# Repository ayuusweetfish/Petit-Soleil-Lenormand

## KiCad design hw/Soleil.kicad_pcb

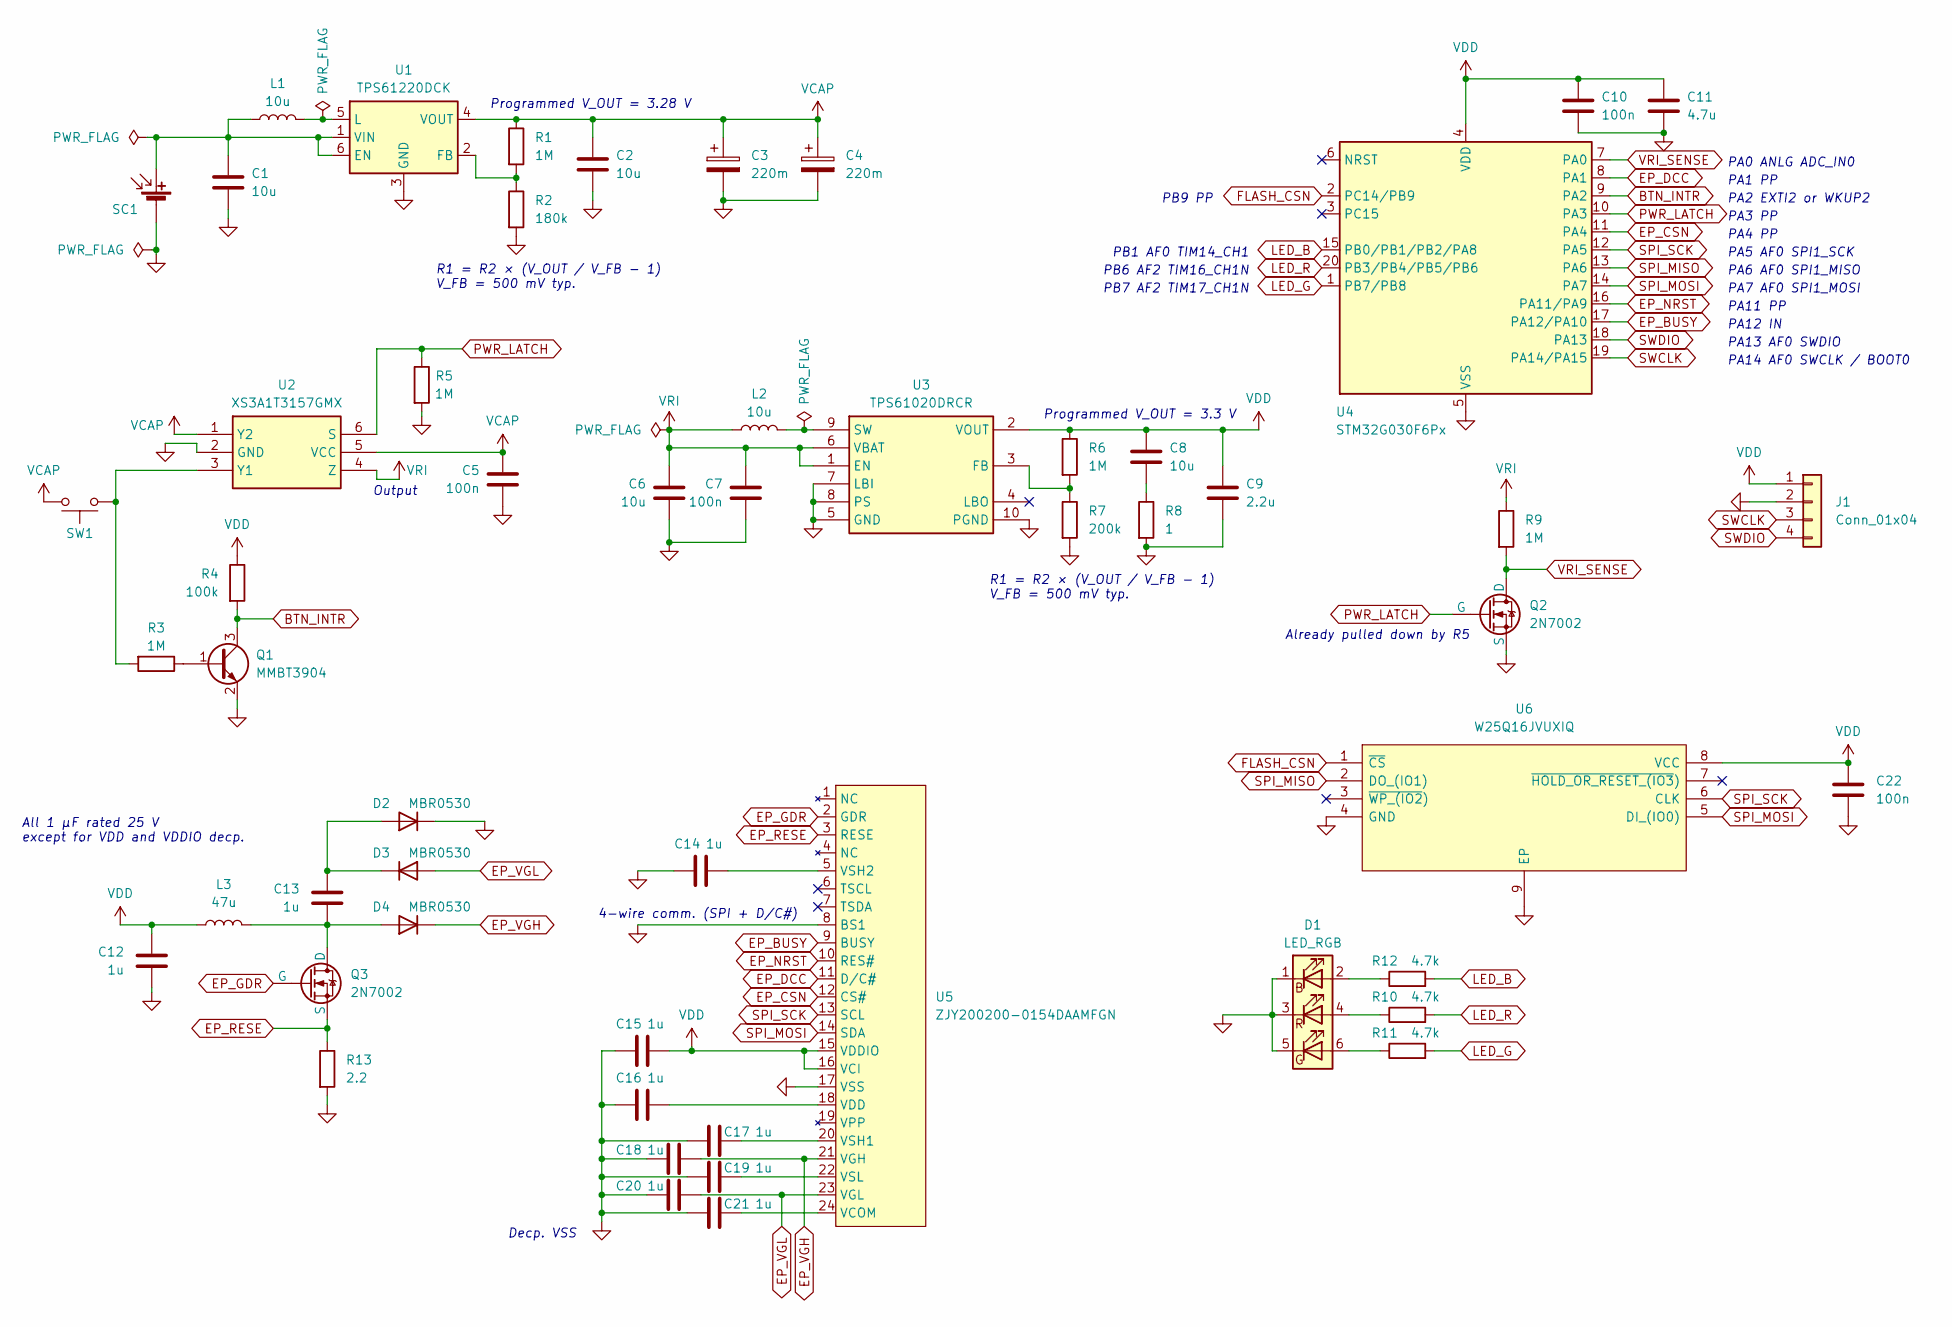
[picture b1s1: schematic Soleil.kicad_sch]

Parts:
C1, C2, C6, C8: 10u; C_0402_1005Metric
C3, C4: 220m; DMS3R3
C5, C7, C10, C22: 100n; C_0402_1005Metric
C9: 2.2u; C_0402_1005Metric
C11: 4.7u; C_0402_1005Metric
C12, C13, C14, C15, C16, C17, C18, C19, C20, C21: 1u; C_0402_1005Metric
D1: LED_RGB; LED_BRG_KA_5050-6
D2, D3, D4: MBR0530; D_SOD-123
J1: Conn_01x04; TestPoints_1x04_P2.0
L1, L2: 10u; L_Sunlord_SWPA252012S
L3: 47u; L_Sunlord_SWPA4020S
Q1: MMBT3904; SOT-23
Q2, Q3: 2N7002; SOT-23
R1, R3, R5, R6, R9: 1M; R_0402_1005Metric
R2: 180k; R_0402_1005Metric
R4: 100k; R_0402_1005Metric
R7: 200k; R_0402_1005Metric
R8: 1; R_0402_1005Metric
R10, R11, R12: 4.7k; R_0402_1005Metric
R13: 2.2; R_0402_1005Metric
SC1: Solar_Cell; SolarPanel_3025
SW1: SW_Push; SW_SPST_TL3342
U1: TPS61220DCK; Texas_R-PDSO-G6
U2: XS3A1T3157GMX; Manufacturer_Part_Number XS3A1T3157GMX; Mouser Part Number 771-XS3A1T3157GMX
U3: TPS61020DRCR; Manufacturer_Part_Number TPS61020DRCR; Mouser Part Number 595-TPS61020DRCR
U4: STM32G030F6Px; TSSOP-20_4.4x6.5mm_P0.65mm
U5: ZJY200200-0154DAAMFGN; FPC_1x24_P0.5
U6: W25Q16JVUXIQ; SON50P300X200X60-9N; Manufacturer_Part_Number W25Q16JVUXIQ

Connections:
BTN_INTR: Q1.3 (C), R4.2, U4.9 (PA2)
EP_BUSY: U4.17 (PA12/PA10), U5.9 (BUSY)
EP_CSN: U4.11 (PA4), U5.12 (CS#)
EP_DCC: U4.8 (PA1), U5.11 (D/C#)
EP_GDR: Q3.1 (G), U5.2 (GDR)
EP_NRST: U4.16 (PA11/PA9), U5.10 (RES#)
EP_RESE: Q3.2 (S), R13.1, U5.3 (RESE)
EP_VGH: C18.2, D4.1 (K), U5.21 (VGH)
EP_VGL: C20.2, D3.2 (A), U5.23 (VGL)
FLASH_CSN: U4.2 (PC14/PB9), U6.1 (~CS)
GND: C1.2, C2.2, C3.2, C4.2, C5.1, C6.2, C7.2, C9.2, C10.1, C11.1, C12.2, C14.1, C15.1, C16.1, C17.1, C18.1, C19.1, C20.1, C21.1, C22.1, D1.1 (BK), D1.3 (RK), D1.5 (GK), D2.1 (K), J1.2, Q1.2 (E), Q2.2 (S), R2.2, R5.2, R7.2, R8.2, R13.2, SC1.2 (-), U1.3 (GND), U2.2 (GND), U3.5 (GND), U3.7 (LBI), U3.8 (PS), U3.10 (PGND), U3.11 (EP/PGND_1), U3.A11 (EP/PGND_2), U3.B11 (EP/PGND_3), U3.C11 (EP/PGND_4), U3.D11 (EP/PGND_5), U4.5 (VSS), U5.8 (BS1), U5.17 (VSS), U6.4 (GND), U6.9 (EP)
LED_B: R12.2, U4.15 (PB0/PB1/PB2/PA8)
LED_G: R11.2, U4.1 (PB7/PB8)
LED_R: R10.2, U4.20 (PB3/PB4/PB5/PB6)
unnamed: C8.2, R8.1
unnamed: D1.2 (BA), R12.1
unnamed: D1.6 (GA), R11.1
unnamed: D1.4 (RA), R10.1
unnamed: C13.1, D2.2 (A), D3.1 (K)
unnamed: C13.2, D4.2 (A), L3.2, Q3.3 (D)
unnamed: Q1.1 (B), R3.1
unnamed: C1.1, L1.1, SC1.1 (+), U1.1 (VIN), U1.6 (EN)
unnamed: R1.2, R2.1, U1.2 (FB)
unnamed: L1.2, U1.5 (L)
unnamed: R3.2, SW1.2, U2.3 (Y1)
unnamed: R6.2, R7.1, U3.3 (FB)
unnamed: L2.2, U3.9 (SW)
unnamed: C21.2, U5.24 (VCOM)
unnamed: C16.2, U5.18 (VDD)
unnamed: C17.2, U5.20 (VSH1)
unnamed: C14.2, U5.5 (VSH2)
unnamed: C19.2, U5.22 (VSL)
PWR_LATCH: Q2.1 (G), R5.1, U2.6 (S), U4.10 (PA3)
SPI_MISO: U4.13 (PA6), U6.2 (DO_(IO1))
SPI_MOSI: U4.14 (PA7), U5.14 (SDA), U6.5 (DI_(IO0))
SPI_SCK: U4.12 (PA5), U5.13 (SCL), U6.6 (CLK)
SWCLK: J1.3, U4.19 (PA14/PA15)
SWDIO: J1.4, U4.18 (PA13)
VCAP: C2.1, C3.1, C4.1, C5.2, R1.1, SW1.1, U1.4 (VOUT), U2.1 (Y2), U2.5 (VCC)
VDD: C8.1, C9.1, C10.2, C11.2, C12.1, C15.2, C22.2, J1.1, L3.1, R4.1, R6.1, U3.2 (VOUT), U4.4 (VDD), U5.15 (VDDIO), U5.16 (VCI), U6.8 (VCC)
VRI: C6.1, C7.1, L2.1, R9.1, U2.4 (Z), U3.1 (EN), U3.6 (VBAT)
VRI_SENSE: Q2.3 (D), R9.2, U4.7 (PA0)

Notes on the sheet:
PA12 IN
Programmed V_OUT = 3.3 V
PB7 AF2 TIM17_CH1N
PA11 PP
PA3 PP
PA7 AF0 SPI1_MOSI
4-wire comm. (SPI + D/C#)
PB6 AF2 TIM16_CH1N
PB1 AF0 TIM14_CH1
PB9 PP
R1 = R2 × (V_OUT / V_FB - 1) V_FB = 500 mV typ.
Decp. VSS
All 1 µF rated 25 V except for VDD and VDDIO decp.
PA1 PP
PA0 ANLG ADC_IN0
PA4 PP
PA5 AF0 SPI1_SCK
Already pulled down by R5
Output
PA14 AF0 SWCLK / BOOT0
PA6 AF0 SPI1_MISO
Programmed V_OUT = 3.28 V
PA2 EXTI2 or WKUP2
PA13 AF0 SWDIO

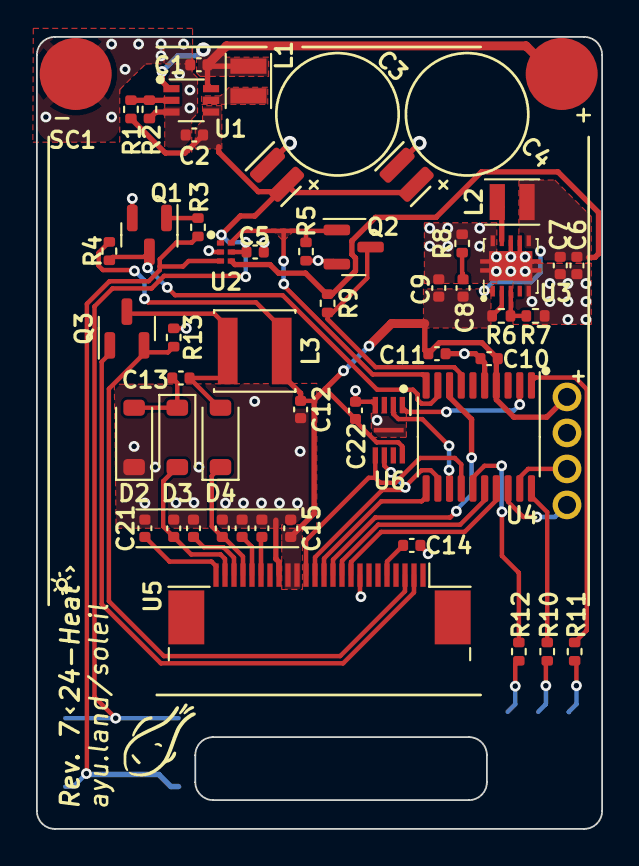
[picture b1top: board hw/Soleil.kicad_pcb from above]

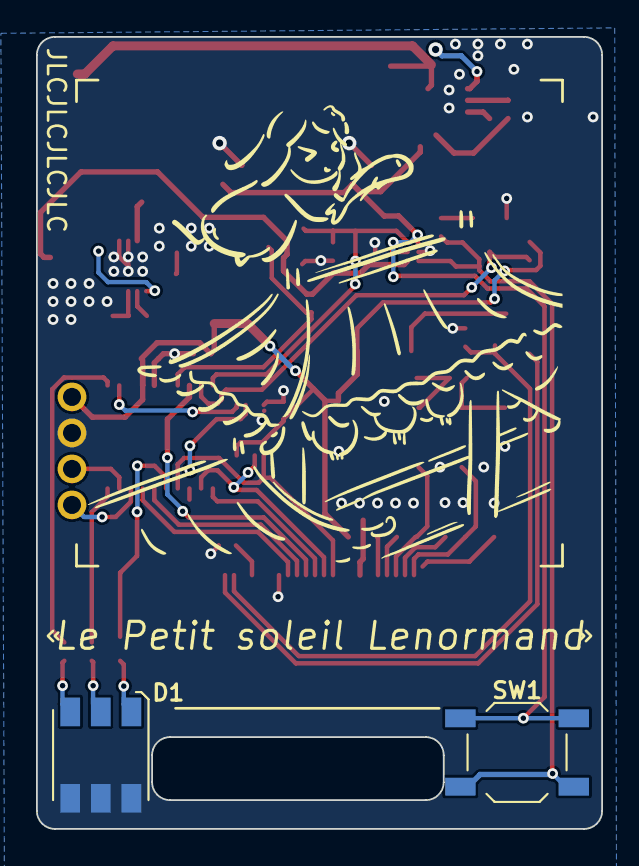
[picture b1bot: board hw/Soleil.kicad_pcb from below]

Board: 2 copper layers, 31.4 x 44.0 mm, 54 parts (2 on the bottom side), 42 nets.

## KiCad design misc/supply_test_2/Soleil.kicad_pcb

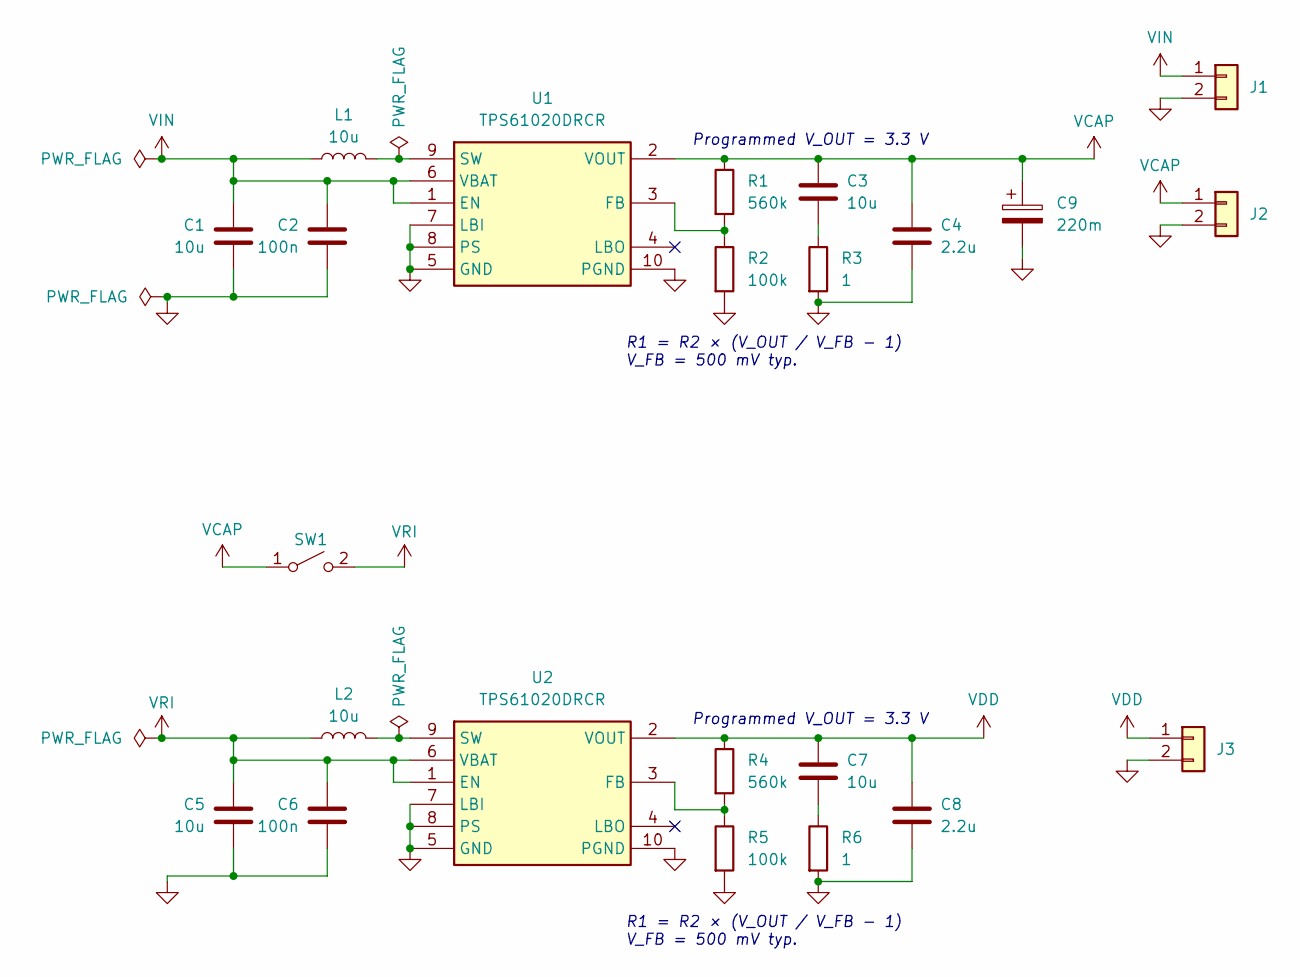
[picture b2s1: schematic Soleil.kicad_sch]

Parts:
C1, C3, C5, C7: 10u; C_0603_1608Metric
C2, C6: 100n; C_0603_1608Metric
C4, C8: 2.2u; C_0603_1608Metric
C9: 220m; DMS3R3
J1, J2, J3: Conn_01x02; PinHeader_1x02_P2.54mm_Vertical
L1, L2: 10u; L_Sunlord_SWPA252012S
R1, R4: 560k; R_0402_1005Metric
R2, R5: 100k; R_0402_1005Metric
R3, R6: 1; R_0402_1005Metric
SW1: SW_SPST; SPST_1x01_P2.54
U1, U2: TPS61020DRCR; Manufacturer_Part_Number TPS61020DRCR; Mouser Part Number 595-TPS61020DRCR

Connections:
GND: C1.2, C2.2, C4.2, C5.2, C6.2, C8.2, C9.2, J1.2, J2.2, J3.2, R2.2, R3.2, R5.2, R6.2, U1.5 (GND), U1.7 (LBI), U1.8 (PS), U1.10 (PGND), U1.11 (EP/PGND_1), U1.A11 (EP/PGND_2), U1.B11 (EP/PGND_3), U1.C11 (EP/PGND_4), U1.D11 (EP/PGND_5), U2.5 (GND), U2.7 (LBI), U2.8 (PS), U2.10 (PGND), U2.11 (EP/PGND_1), U2.A11 (EP/PGND_2), U2.B11 (EP/PGND_3), U2.C11 (EP/PGND_4), U2.D11 (EP/PGND_5)
unnamed: C3.2, R3.1
unnamed: C7.2, R6.1
unnamed: R1.2, R2.1, U1.3 (FB)
unnamed: L1.2, U1.9 (SW)
unnamed: R4.2, R5.1, U2.3 (FB)
unnamed: L2.2, U2.9 (SW)
VCAP: C3.1, C4.1, C9.1, J2.1, R1.1, SW1.1 (A), U1.2 (VOUT)
VDD: C7.1, C8.1, J3.1, R4.1, U2.2 (VOUT)
VIN: C1.1, C2.1, J1.1, L1.1, U1.1 (EN), U1.6 (VBAT)
VRI: C5.1, C6.1, L2.1, SW1.2 (B), U2.1 (EN), U2.6 (VBAT)

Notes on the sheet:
Programmed V_OUT = 3.3 V
R1 = R2 × (V_OUT / V_FB - 1) V_FB = 500 mV typ.

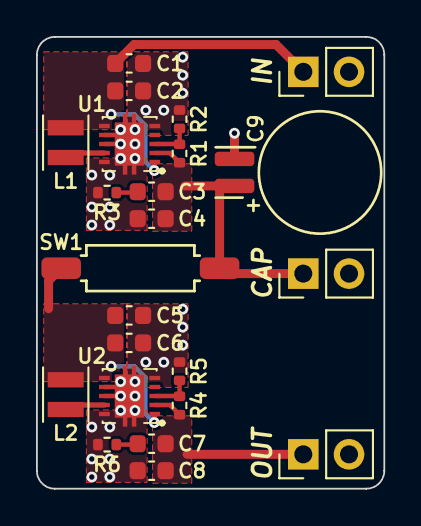
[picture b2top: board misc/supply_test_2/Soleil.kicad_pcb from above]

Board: 2 copper layers, 19.3 x 25.1 mm, 23 parts (0 on the bottom side), 11 nets.

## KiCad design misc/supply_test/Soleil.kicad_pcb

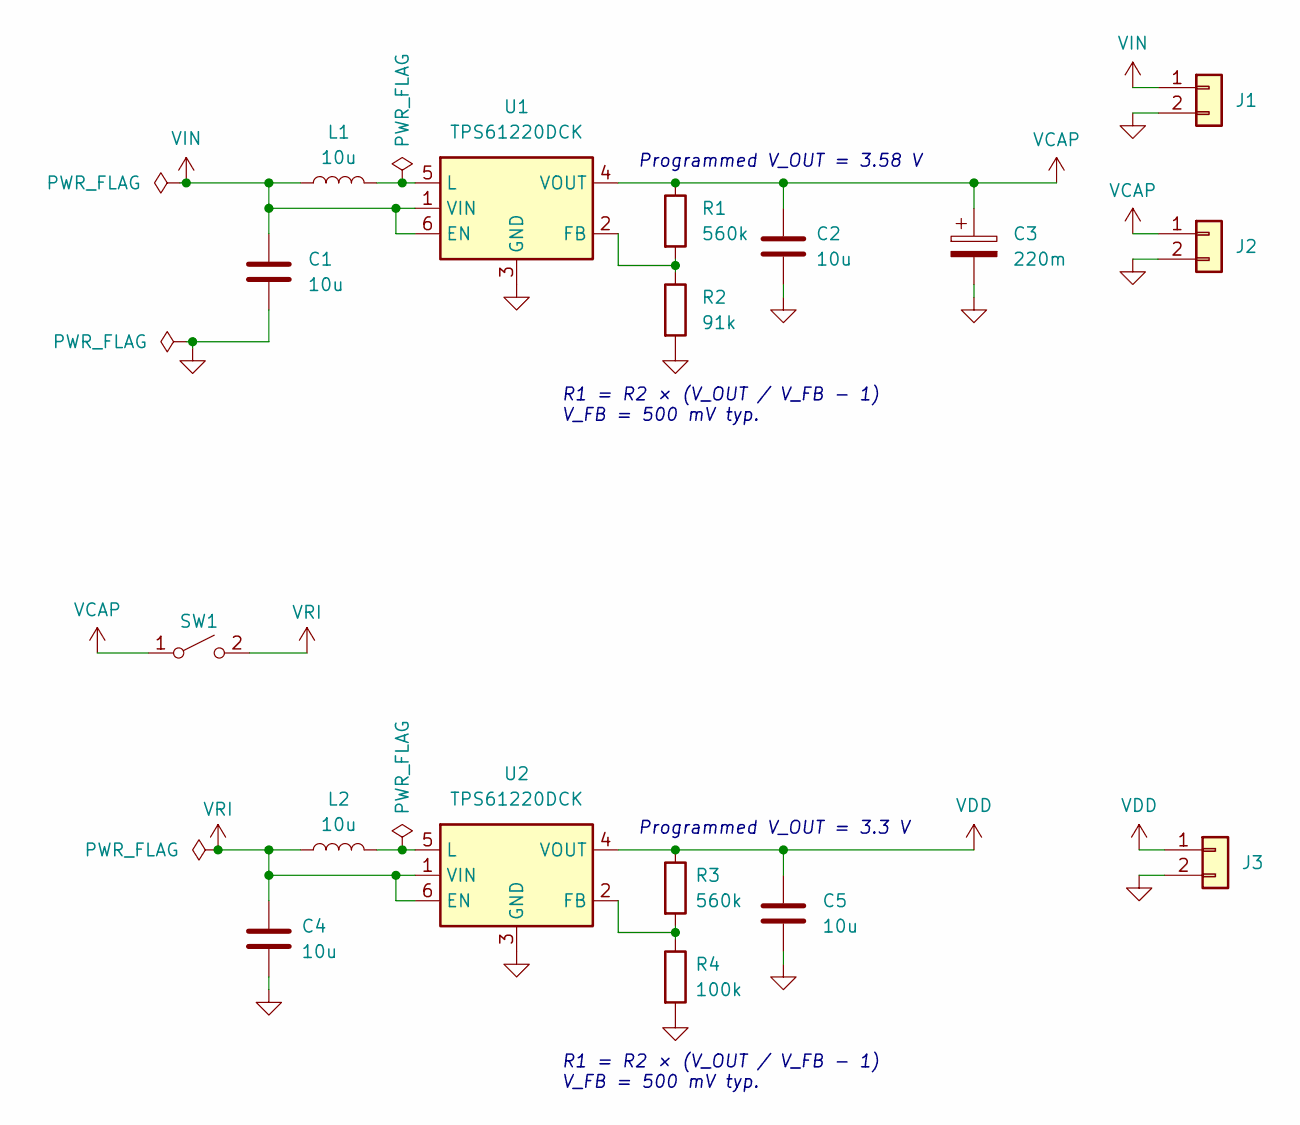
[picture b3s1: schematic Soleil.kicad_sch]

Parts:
C1, C2, C4, C5: 10u; C_0603_1608Metric
C3: 220m; DMS3R3
J1, J2, J3: Conn_01x02; PinHeader_1x02_P2.54mm_Vertical
L1, L2: 10u; L_Sunlord_SWPA252012S
R1, R3: 560k; R_0603_1608Metric
R2: 91k; R_0603_1608Metric
R4: 100k; R_0603_1608Metric
SW1: SW_SPST; SPST_1x01_P2.54
U1, U2: TPS61220DCK; Texas_R-PDSO-G6

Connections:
GND: C1.2, C2.2, C3.2, C4.2, C5.2, J1.2, J2.2, J3.2, R2.2, R4.2, U1.3 (GND), U2.3 (GND)
unnamed: R1.2, R2.1, U1.2 (FB)
unnamed: L1.2, U1.5 (L)
unnamed: R3.2, R4.1, U2.2 (FB)
unnamed: L2.2, U2.5 (L)
VCAP: C2.1, C3.1, J2.1, R1.1, SW1.1 (A), U1.4 (VOUT)
VDD: C5.1, J3.1, R3.1, U2.4 (VOUT)
VIN: C1.1, J1.1, L1.1, U1.1 (VIN), U1.6 (EN)
VRI: C4.1, L2.1, SW1.2 (B), U2.1 (VIN), U2.6 (EN)

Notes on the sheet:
Programmed V_OUT = 3.58 V
R1 = R2 × (V_OUT / V_FB - 1) V_FB = 500 mV typ.
Programmed V_OUT = 3.3 V

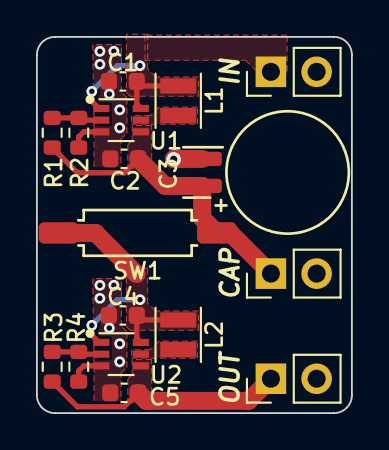
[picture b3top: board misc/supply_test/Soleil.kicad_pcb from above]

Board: 2 copper layers, 17.5 x 20.9 mm, 17 parts (0 on the bottom side), 9 nets.

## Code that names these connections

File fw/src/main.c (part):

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#include "../misc/rng/twofish.h"
#include "../misc/rng/xoodoo.h"

#define PIN_LED_R     GPIO_PIN_4
#define PIN_LED_G     GPIO_PIN_7
#define PIN_LED_B     GPIO_PIN_1
#define PIN_EP_NCS    GPIO_PIN_4
#define PIN_EP_DCC    GPIO_PIN_1
#define PIN_EP_NRST   GPIO_PIN_11
#define PIN_EP_BUSY   GPIO_PIN_12
#define EXTI_LINE_EP_BUSY EXTI_LINE_12
#define PIN_BUTTON    GPIO_PIN_2
#define EXTI_LINE_BUTTON  EXTI_LINE_2
#define PIN_PWR_LATCH GPIO_PIN_3

#include "debug_printf.h"

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static inline void _epd_cmd(uint8_t cmd, const uint8_t *params, size_t params_size)
{
  HAL_GPIO_WritePin(GPIOA, PIN_EP_NCS, GPIO_PIN_RESET);
  HAL_GPIO_WritePin(GPIOA, PIN_EP_DCC, GPIO_PIN_RESET);
  spi_transmit(&cmd, 1);
  HAL_GPIO_WritePin(GPIOA, PIN_EP_DCC, GPIO_PIN_SET);
  if (params_size > 0) {
    spi_transmit(params, params_size);
  }
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static inline void epd_read(uint8_t cmd, uint8_t *out_buf, size_t out_buf_size)
{
  HAL_GPIO_WritePin(GPIOA, PIN_EP_NCS, GPIO_PIN_RESET);
  HAL_GPIO_WritePin(GPIOA, PIN_EP_DCC, GPIO_PIN_RESET);
  spi_transmit(&cmd, 1);
  HAL_GPIO_WritePin(GPIOA, PIN_EP_DCC, GPIO_PIN_SET);
  spi_receive(out_buf, out_buf_size);
  HAL_GPIO_WritePin(GPIOA, PIN_EP_NCS, GPIO_PIN_SET);
}

static inline void epd_waitbusy()
{
  // Wait for PIN_EP_BUSY to go low

  sleep_delay(2); // Some operations are short, branch off early

  while (GPIOA->IDR & PIN_EP_BUSY) {
#if ENABLE_SLEEP
    HAL_SuspendTick();
    rtc_waiting_for = RTC_WAITING_FOR_EP_BUSY;
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
    // If the busy pin is still actually high, enter Stop 1 mode
    PWR->CR1 = (PWR->CR1 & ~PWR_CR1_LPMS) | PWR_CR1_LPMS_0;
    if (GPIOA->IDR & PIN_EP_BUSY) {
      SCB->SCR |= SCB_SCR_SLEEPDEEP_Msk;
      __WFI();
      SCB->SCR &= ~SCB_SCR_SLEEPDEEP_Msk;
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static void epd_reset(bool partial, bool power_save)
{
  // (1) HW & SW Reset
  HAL_GPIO_WritePin(GPIOA, PIN_EP_NRST, GPIO_PIN_RESET);
  sleep_delay(10);
  HAL_GPIO_WritePin(GPIOA, PIN_EP_NRST, GPIO_PIN_SET);
  sleep_delay(10);
  epd_waitbusy();
  // SW RESET
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
  uint8_t cmd = 0x27;
  HAL_GPIO_WritePin(GPIOA, PIN_EP_NCS, GPIO_PIN_RESET);
  HAL_GPIO_WritePin(GPIOA, PIN_EP_DCC, GPIO_PIN_RESET);
  spi_transmit(&cmd, 1);
  HAL_GPIO_WritePin(GPIOA, PIN_EP_DCC, GPIO_PIN_SET);
  spi_receive((uint8_t *)ram, 1); // Dummy byte
  for (int i = 0; i < 32; i++) {
    spi_receive((uint8_t *)ram, n * 4);
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  __HAL_RCC_GPIOB_CLK_ENABLE();
  GPIO_InitTypeDef gpio_init;

  // SWD (PA13, PA14)
  gpio_init.Pin = GPIO_PIN_13 | GPIO_PIN_14;
  gpio_init.Mode = GPIO_MODE_AF_PP; // Pass over control to AF peripheral
  gpio_init.Alternate = GPIO_AF0_SWJ;
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
  // ======= Power latch ======
  gpio_init = (GPIO_InitTypeDef){
    .Pin = PIN_PWR_LATCH,
    .Mode = GPIO_MODE_OUTPUT_PP,
    .Pull = GPIO_NOPULL,
    .Speed = GPIO_SPEED_FREQ_LOW,
  };
  HAL_GPIO_Init(GPIOA, &gpio_init);
  HAL_GPIO_WritePin(GPIOA, PIN_PWR_LATCH, 1);

  // ======== Clocks ========
  setup_clocks();
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
  // Activate EPD driver (SSD1681) reset signal
  gpio_init = (GPIO_InitTypeDef){
    .Pin = PIN_EP_NRST,
    .Mode = GPIO_MODE_OUTPUT_PP,
    .Pull = GPIO_NOPULL,
    .Speed = GPIO_SPEED_FREQ_LOW,
  };
  HAL_GPIO_Init(GPIOA, &gpio_init);
  HAL_GPIO_WritePin(GPIOA, PIN_EP_NRST, 0);

  // ======== Button ========
  gpio_init.Pin = PIN_BUTTON;
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    uint32_t t0 = HAL_GetTick();
    while (GPIOA->IDR & PIN_BUTTON) {
      if (HAL_GetTick() - t0 >= timeout_seconds * 1000) {
        HAL_GPIO_WritePin(GPIOA, PIN_PWR_LATCH, 0);
        while (1) { }
      }
    }
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
  // ======== SPI ========
  // GPIO ports
  // SPI1_SCK (PA5), SPI1_MISO (PA6), SPI1_MOSI (PA7)
  gpio_init.Pin = GPIO_PIN_5 | GPIO_PIN_6 | GPIO_PIN_7;
  gpio_init.Mode = GPIO_MODE_AF_PP;
  gpio_init.Alternate = GPIO_AF0_SPI1;
  gpio_init.Pull = GPIO_NOPULL;
  gpio_init.Speed = GPIO_SPEED_FREQ_HIGH;
  HAL_GPIO_Init(GPIOA, &gpio_init);
  // Output FLASH_CSN (PB9)
  HAL_GPIO_Init(GPIOB, &(GPIO_InitTypeDef){
    .Pin = GPIO_PIN_9,
    .Mode = GPIO_MODE_OUTPUT_PP,
  });
  HAL_GPIO_WritePin(GPIOB, GPIO_PIN_9, 1);
  // Output EP_CSN (PA4), EP_DCC (PA6 (Rev. 4) / PA1 (Rev. 5))
  // EP_NRST (PA11) is initialised earlier
  gpio_init.Pin = PIN_EP_NCS | PIN_EP_DCC;
  gpio_init.Mode = GPIO_MODE_OUTPUT_PP;
  gpio_init.Pull = GPIO_NOPULL;
  HAL_GPIO_Init(GPIOA, &gpio_init);
  HAL_GPIO_WritePin(GPIOA, PIN_EP_NCS, 1);
  // while (HAL_GPIO_ReadPin(GPIOA, PIN_EP_NCS) == 0) { }
  HAL_GPIO_WritePin(GPIOA, PIN_EP_DCC, 0);
  HAL_GPIO_WritePin(GPIOA, PIN_EP_NRST, 0);
  // Input EP_BUSY (PA12)
  gpio_init.Pin = PIN_EP_BUSY;
  gpio_init.Mode = GPIO_MODE_INPUT;
  gpio_init.Pull = GPIO_PULLDOWN;
  HAL_GPIO_Init(GPIOA, &gpio_init);
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    // EPD
    if (n_cards == 1) {
      if (epd_state == 0 && t >= 30) {
        HAL_GPIO_WritePin(GPIOA, PIN_EP_NRST, GPIO_PIN_RESET);
        epd_state = 1;
      } else if (epd_state == 1 && t >= 50) {
        HAL_GPIO_WritePin(GPIOA, PIN_EP_NRST, GPIO_PIN_SET);
        epd_state = 2;
      } else if (epd_state == 2 && t >= 70) {
        epd_waitbusy();
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
if (0) {
  display_image(-1);
  HAL_GPIO_WritePin(GPIOA, PIN_PWR_LATCH, 0);
  while (1) { }
}

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    }
  }

  HAL_GPIO_WritePin(GPIOA, PIN_PWR_LATCH, 0);
  HAL_SuspendTick();
  HAL_PWR_EnterSTOPMode(PWR_LOWPOWERREGULATOR_ON, PWR_STOPENTRY_WFI);
  while (1) { }
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    setup_clocks();
    stopped = false;
  }
  __HAL_GPIO_EXTI_CLEAR_IT(PIN_EP_BUSY);
}

void TIM3_IRQHandler()
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  else return;

  HAL_GPIO_Init(GPIOB, &(GPIO_InitTypeDef){
    .Pin = PIN_LED_R,
    .Mode = GPIO_MODE_OUTPUT_PP,
  });
  if (rtc_waiting_for == RTC_WAITING_FOR_BTN) {
    // Turn off
    HAL_GPIO_WritePin(GPIOA, PIN_PWR_LATCH, 0);
    // Indicate status when the debug probe is connected
    for (int i = 0; ; i++) {
      GPIOB->BSRR = PIN_LED_R << 16; spin_delay(16000 * 40);
      GPIOB->BSRR = PIN_LED_R <<  0; spin_delay(16000 * 40);
    }
  } else if (rtc_waiting_for == RTC_WAITING_FOR_EP_BUSY) {
    // EPD busy stays high, try system reset (most probably a soldering defect!)
    for (int i = 0; i < 5; i++) {
      GPIOB->BSRR = PIN_LED_R <<  0; spin_delay(16000 * 40);
      GPIOB->BSRR = PIN_LED_R << 16; spin_delay(16000 * 40);
    }
    NVIC_SystemReset();
  }
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
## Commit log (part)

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2023-11-28 🎉 Blink
2023-11-28 Writing EPD
2023-11-28 Read ADC
2023-11-28 Release power latch after 10 blinks
2023-11-28 Write display and power off
2023-12-23 Sort-out; add hardware design
2023-12-23 (WIP) Update PCB layout, routing to-do
2023-12-23 Finish routing for the updated board
2023-12-23 Change LED to SMD RGB; submit for fabrication
2023-12-23 Add CAD files for EPD dimensions
2023-12-31 Blink on the updated hardware
2024-01-03 Test RGB LED PWM output with rotating hues
2024-02-29 Revise schematic
2024-02-29 Revise circuit board design; submit for fab
2024-03-08 Update firmware to match revised hardware
2024-03-08 Enable PLL; add pauses between lighting cycles
2024-03-09 Enable EXTI interrupt
2024-03-09 Enter Stop mode and wake up by button press
2024-03-09 Enter Stop 1 mode when idle and resume on button press
2024-03-09 Update EPD (?)
2024-03-09 Fix corrupted memory
2024-03-09 Inspect entropy sources
2024-03-09 Add SRAM state as an entropy source
2024-03-12 Add back partial refreshes
2024-03-12 Count LSI as an entropy source
2024-03-15 Revise and simplify schematic
2024-03-16 Revise board design; submit for fab (Rev. 5)
2024-03-17 Read factory clock calibration as a source of device signature
2024-03-18 Add Twofish implementation
2024-03-18 Switch to Brian Gladman's Twofish implementation
2024-03-18 Adapt Twofish impl. as a header-only library
2024-03-19 Add satellite images
2024-03-19 Add Meteosat IR data from EUMETSAT
2024-03-19 Extend sources by multiple data endpoints from each entity
2024-03-19 Normalise all returned payload to Uint8Array
2024-03-19 Use SHAKE256 for an overall digest
2024-03-19 (WIP) Periodic checks
2024-03-19 Use `Deno.cron` for scheduling
2024-03-20 Implement running pre-commitment
2024-03-20 Save miscellaneous random blocks
2024-03-20 Properly report rejections in misc. block crafting
2024-03-20 Fix too recent timestamp for misc. entropy collection
2024-03-20 Add FY WV back to public sources with timestamp offset
2024-03-20 Fix misspelled Cron schedule
2024-03-20 Eliminate redundant initialization on startup
2024-03-21 Mix in previous output
2024-03-21 Load previous block on startup
2024-03-21 Trace back in time for backup/debug usage
2024-03-21 (WIP) Adapt firmware pin definitions to Rev. 5 hardware
2024-03-21 Add HTTP endpoint
2024-03-21 Report error messages on currently missing sources
2024-03-21 Added short and plain formatted endpoints
2024-03-21 Report previous pulse at root URL
2024-03-21 Fix romanticisation of Elektro-L
2024-03-21 Properly store messages and image URLs
2024-03-21 Keep reporting source URLs for current pulse after finalisation
2024-03-21 Fix falsely reporting null output for current pulse on distributed deploy environments
2024-03-22 🚧 Debugging hardware
2024-03-23 Revise hardware; fix phantom powering
2024-03-23 🚧 Further revise hardware
2024-03-23 Revise hardware and submit for fabrication (Rev. 6)
2024-03-25 Add Ayu.land log digest as a miscellaneous source
2024-03-25 Add webpage placeholders
2024-03-26 Keep URLs and messages for 24 hours
2024-03-26 Serve static page contents
2024-03-26 Automatically process and subset font
2024-03-27 Tweak page appearance on mobile devices
2024-03-27 Add OpenSky Network as a miscellaneous source
2024-03-28 Add hash verification implementation in C
2024-03-28 Simplify C implementation
2024-03-28 Implement lookup-based web page template
2024-03-28 Add monospace text
2024-03-28 Add complete verification steps to the page
2024-03-28 Fix incorrect precommitment check instruction
2024-03-29 Cache images from INSAT
2024-03-29 Display timestamps on web page
2024-03-29 Log modification timestamps and sizes of fetched images
2024-03-29 Use full font file during development
2024-03-29 Add banner background image
2024-03-30 Revise web page
2024-03-30 Fix large files not written to cache database
2024-03-30 Implement a file cache server
2024-03-30 Migrate to the external cache server
2024-03-30 A few clean-up fixes
2024-03-30 More clean-up fixes
2024-03-30 More > <
2024-03-30 Fix incongruences in the C hash implementation
2024-03-30 Automatically prune cached files older than a day
2024-03-31 Support multiple pages
2024-03-31 Revise web pages
2024-03-31 Add titles to pages
2024-03-31 Store language selection in cookies
2024-03-31 Minor appearance tweaks
2024-03-31 Keep mixing in the last pulse with possibly skipped ones
2024-03-31 Workaround for frozen cron jobs on Deploy?
2024-03-31 Fix SDO/AIA 193 misc. source rejected due to timestamp offset
2024-04-01 Cache template lookup from previous pulse
2024-04-01 Tweak web pages
2024-04-03 Test with STOP mode on startup
2024-04-03 Debug switch erroneously left on
2024-04-05 Replace INSAT source with a more frequently updated one
2024-04-05 Deutscher Wetterdienst's WMC?
2024-04-06 🚧 Update beacon web page
2024-04-06 Minor page style fixes
2024-04-07 Proxy emojis
2024-04-07 Why edit the pages yet another time?
2024-05-31 Add power supply test (Rev. 6/T)
2024-05-31 Revise text style; submit for fab
2024-07-13 Add supply test 2 (with TPS61020)
2024-07-17 Add minimal power consumption test firmware
2024-07-17 Revise main firmware with testing interactions?
2024-07-18 Update layout, 🚧 routing to-do
2024-07-19 Finish board routing
2024-07-23 Drive power latch high in firmware
2024-07-23 Correctly working!!
2024-07-31 Keep refreshing EPD to ease debugging...?
2024-08-01 Adjust EPD voltage levels to reduce current consumption!
2024-08-01 Keep both clear and power-save modes
2024-08-03 🚧 Use default EPD refresh strength for testing
2024-08-04 Revise testing behaviour
    Wait for a button press before partial refresh
2024-08-06 Add missing run-length encoder program
2024-08-06 Correctly read ADC value
2024-08-06 Firmware source clean-ups
2024-08-06 Raise LED PWM frequency to 4 kHz again
2024-08-06 Print voltage on screen
2024-08-07 Display entropy values on screen
2024-08-07 More entropy
2024-08-07 Use power-save mode with low battery
2024-08-08 Attempts at reducing current consumption
2024-08-25 Convert bitmap font to blob
2024-08-25 Compress glyph data
2024-08-25 Render glyphs!
2024-08-25 Read flash IC identifier
2024-08-25 Correctly read font data from flash IC
2024-08-25 Correctly displaying glyphs!
2024-08-25 Print strings with the bitmap font
2024-08-27 Batch-write card titles
2024-08-27 🚧 Combine cards data into a binary file
2024-08-27 🎉 Reading and displaying images and overlays from flash!
2024-08-27 Display text
2024-08-27 🔮 Randomise!
2024-08-28 Random number generator test
2024-08-28 More revisions to PRNG
2024-08-28 Mix in TIM3 during ADC entropy accumulation
2024-08-28 Minor revision to EPD greyscale
2024-08-28 🚧 How to correctly use this greyscale waveform?
2024-08-28 Cannot adjust for a lighter grey; reverting
2024-08-28 Revert "🚧 How to correctly use this greyscale waveform?"
    This reverts commit a8e2c3f7c570e677563b1503fb4a05057738aff8.
2024-08-29 Card names on different sides
2024-08-29 Separate outline and shadow images! 💐
2024-08-29 Cleaner text after images
2024-08-29 More illustrations?!
2024-08-30 Revise existing illustrations
2024-08-30 Poke around with timers
2024-08-30 Switch red LED to TIM3, freeing up TIM16 for LSI entropy
2024-08-31 Add Krita plugin for exporting images
2024-08-31 Fix exported image sizes and backgrounds
2024-08-31 Fix Moon card illustration (draft accidentally included)
2024-08-31 More accurate spin delay subroutine
2024-08-31 Revamp entropy collectors
2024-08-31 Shrink entropy pool size and duration for collection
2024-08-31 Revamp entropy accumulation scheme
2024-08-31 Throttling on button release detection
2024-08-31 Start the lights as soon as possible
2024-08-31 Fade out the magical light
2024-09-01 Mildly reduce duplication
2024-09-01 Cycle between graphic pages
2024-09-01 Switch to Xoodoo for cryptographic permutation
2024-09-01 Record time spent in entropy accumulation (for debug use)
2024-09-01 Revamp button interaction logic
2024-09-01 Take entropy from button interactions
2024-09-01 🚧 RTC??
2024-09-02 Implement 2 minutes power-off timeout by RTC
2024-09-02 Draw a new card with a long key press (revised button debouncing)
2024-09-02 Looping pages!
2024-09-03 Work around a crazy defect (/_<)
2024-09-03 Minor clean-ups
2024-09-11 🚧 Try to read floating SWD pins (not employing)
2024-09-11 Reading captured timer counts through interrupts
2024-09-11 Revert previous changes; revise clock jitter entropy algorithm (sync Luminography)
2024-09-11 Minor revisions (lights, sampling frequency, extra whitening by jitter entropy)
2024-09-12 Reimplement RAM entropy subroutine with explicit registers
2024-09-12 Fix RAM entropy accumulation subroutine infinite loop
2024-09-12 Revisions to clocks and lights (randomise initial phase)
2024-09-12 Refactor away division at every timer period
2024-09-12 Deep sleep during EPD busy wait? (With glitches)
2024-09-12 Revert to sleep-delay for busy wait
2024-09-12 Fix waiting in stop mode by debouncing the signal
2024-09-12 Place flash IC into sleep mode whenever proper
2024-09-13 Incorporate EPD RAM into entropy pool
2024-09-13 Incorporate EPD read into the flashing lights
2024-09-13 (Untested) Add floating pin entropy source
2024-09-13 Revise card name SVG
2024-09-13 🚧 Incorporate floating pins into pool
2024-09-13 Might be partly fixing floating pin entropy (see comments)
2024-09-13 🚧 Trying to reduce redundant ADC operations
2024-09-14 Adapt all ADC operations to the register-access subroutines
2024-09-14 Fix ADC channel > 16 incorrectly inaccessible
    Incorporating floating-pin entropy into continuous samples
2024-09-14 Add halt debug command
2024-09-14 Correct title layout for all sides
2024-09-14 Revise illustration for the Shadow card
2024-09-14 Calculate floating pin randomness with RCC
2024-09-14 Squeeze more entropy from the floating pin
2024-09-17 Move cards directory up to root
2024-09-19 Vary letter spacing in card titles
2024-09-21 Add Rider illustration; minor revisions to existing ones
2024-09-30 Handle prolonged key presses during sleep
    Also, overlay voltage on illustration for quicker inspection and clean up comments
2024-10-02 Testing for power consumption at idle
2024-12-04 Add stop-mode test for current consumption test
2024-12-06 Place flash in power-down in stop-mode test
2024-12-07 Disable GPIO pins in stop-mode test
2025-09-28 Switch Elekto-L images to HTTPS
2025-09-28 Tighten Elektro-L lag amount
2025-09-28 beacon: Fix crash due to source name migration
2025-09-28 beacon: Fix bootstrapping crash
2025-09-29 beacon: Use half-hour older INSAT-3DS data
2025-09-29 beacon: Amend incorrect last commit
2026-01-03 fw: Migrate to plain Makefile
    Ref: ayuusweetfish/AICHO:17ed03a (25a)
2026-01-03 fw: Debugging support
2026-01-03 fw: Use `make debug` for debugging session
2026-01-03 fw: Further trim Makefile
2026-01-03 misc: Rebuild card names SVG/PNG
2026-01-03 misc: Tweak card name appearance
2026-01-03 misc: Rebuild SPI flash image?
    (Untested; offset differs from source)
2026-01-03 fw: A few switches to ease debugging
2026-01-03 misc: Add a script to dump SPI flash content
2026-01-05 fw, misc: Build SPI flash image with Makefile
2026-01-05 fw, misc: Move all flash image build files to `BDIR`
2026-01-05 fw, misc: Further normalize Makefile and helper programs
2026-01-06 fw, misc: Move test programs to dedicated directory
2026-01-06 fw, misc: Comprehensively test Xoodoo with Xoodyak
2026-01-07 misc: Build binary image for SPI flash content
2026-01-08 fw: Integrate PyOCD configuration into Makefile; add `print-uid` target
2026-01-08 fw: Reset halt before flash erase to get out of interesting system state
    Possible error messages:
    - target was not halted as expected after calling flash algorithm routine (IPSR=3)
    - flash erase all failure (result code 0x40022000)
2026-01-08 fw: Fix uncleared SPI FIFO causing shifted image
    Ref: `stm32g0xx_hal_spi.c`: `SPI_EndRxTransaction()` -> `SPI_WaitFifoStateUntilTimeout()`
2026-06-28 beacon: Start over >_<
2026-06-28 beacon: Add Meteosat
2026-06-28 beacon: Pick a few more data series
2026-06-28 beacon: Add Arktika-M
    These seem to have daily pause periods; errors are expected
2026-06-28 beacon: Bring back SHA-3-224
2026-06-29 beacon: Parallel oracle
